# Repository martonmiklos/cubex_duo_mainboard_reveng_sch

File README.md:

# 3D systems CubeX DUO reverse engineered schematic
Reverse engineered schematics for the 3D system's CubeX DUO 3D printer mainboard.

Drawn in Autodesk EAGLE 9.x

Only the stepper drivers for the main axes and the LCD connector have been reverse engineered yet. 

Our goal was to create a simple step-dir driver from the board.

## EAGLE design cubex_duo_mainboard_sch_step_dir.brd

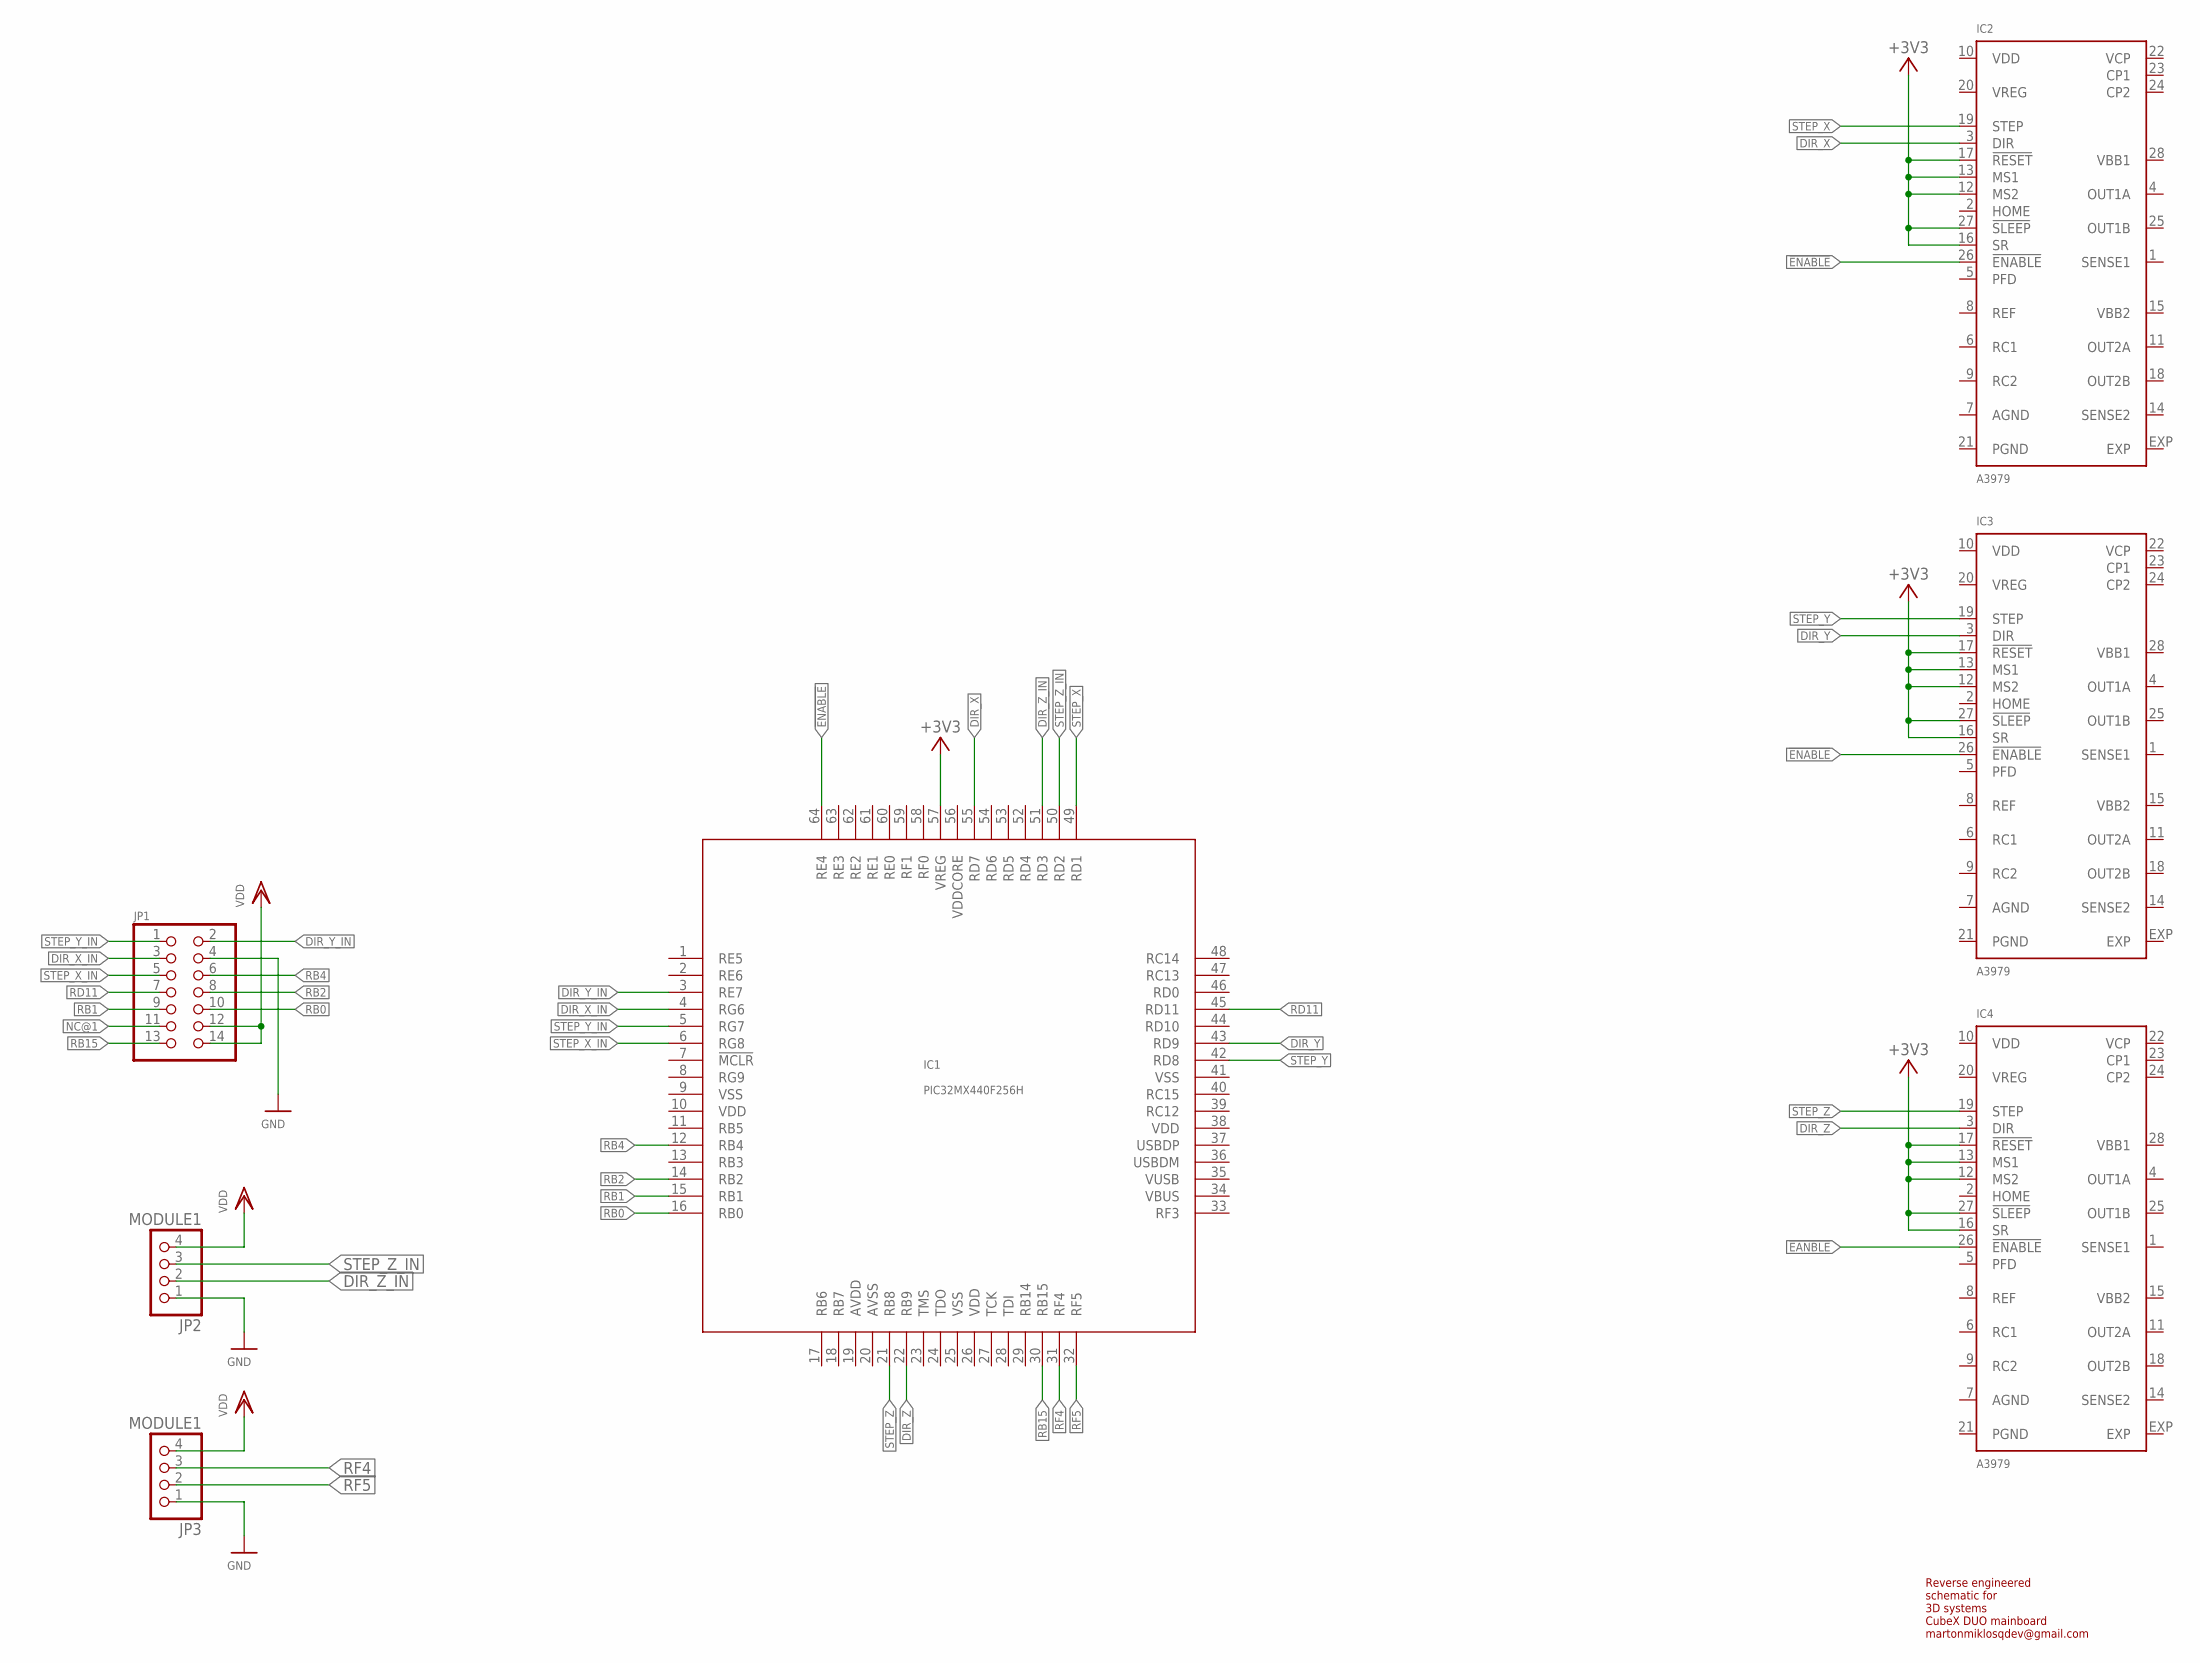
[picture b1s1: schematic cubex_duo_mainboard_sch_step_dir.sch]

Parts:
IC1: PIC32MX440F256H; TQFP64-10X10
IC2, IC3, IC4: A3979; TSSOP28
JP1: PINHD-2X7; 2X07
JP2, JP3: MODULE1; 1X04

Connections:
!EANBLE: IC4.26 (!ENABLE)
!ENABLE: IC1.64 (RE4), IC2.26 (!ENABLE), IC3.26 (!ENABLE)
+3V3: IC1.57 (VREG), IC2.12 (MS2), IC2.13 (MS1), IC2.16 (SR), IC2.17 (!RESET), IC2.27 (!SLEEP), IC3.12 (MS2), IC3.13 (MS1), IC3.16 (SR), IC3.17 (!RESET), IC3.27 (!SLEEP), IC4.12 (MS2), IC4.13 (MS1), IC4.16 (SR), IC4.17 (!RESET), IC4.27 (!SLEEP)
AGND: IC2.7 (AGND), IC3.7 (AGND), IC4.7 (AGND)
AVDD: IC1.19 (AVDD)
AVSS: IC1.20 (AVSS)
DIR_X: IC1.55 (RD7), IC2.3 (DIR)
DIR_X_IN: IC1.4 (RG6), JP1.3
DIR_Y: IC1.43 (RD9), IC3.3 (DIR)
DIR_Y_IN: IC1.3 (RE7), JP1.2
DIR_Z: IC1.22 (RB9), IC4.3 (DIR)
DIR_Z_IN: IC1.51 (RD3), JP2.2
EXP: IC2.EXP, IC3.EXP, IC4.EXP
GND: JP1.4, JP2.1, JP3.1
NC@1: JP1.11
PGND: IC2.21 (PGND), IC3.21 (PGND), IC4.21 (PGND)
RB0: IC1.16 (RB0), JP1.10
RB1: IC1.15 (RB1), JP1.9
RB2: IC1.14 (RB2), JP1.8
RB4: IC1.12 (RB4), JP1.6
RB15: IC1.30 (RB15), JP1.13
RD11: IC1.45 (RD11), JP1.7
RF4: IC1.31 (RF4), JP3.3
RF5: IC1.32 (RF5), JP3.2
STEP_X: IC1.49 (RD1), IC2.19 (STEP)
STEP_X_IN: IC1.6 (RG8), JP1.5
STEP_Y: IC1.42 (RD8), IC3.19 (STEP)
STEP_Y_IN: IC1.5 (RG7), JP1.1
STEP_Z: IC1.21 (RB8), IC4.19 (STEP)
STEP_Z_IN: IC1.50 (RD2), JP2.3
VBB1: IC2.28 (VBB1), IC3.28 (VBB1), IC4.28 (VBB1)
VBB2: IC2.15 (VBB2), IC3.15 (VBB2), IC4.15 (VBB2)
VDD: IC1.10 (VDD), IC1.26 (VDD), IC1.38 (VDD), IC2.10 (VDD), IC3.10 (VDD), IC4.10 (VDD), JP1.12, JP1.14, JP2.4, JP3.4
VDDCORE: IC1.56 (VDDCORE)
VREG: IC2.20 (VREG), IC3.20 (VREG), IC4.20 (VREG)
VSS: IC1.9 (VSS), IC1.25 (VSS), IC1.41 (VSS)

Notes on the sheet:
Reverse engineered schematic for 3D systems CubeX DUO mainboard martonmiklosqdev@gmail.com

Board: 2 copper layers, 7 parts (0 on the bottom side), 31 nets, no tracks yet.

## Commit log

2018-10-26 - Repo init
2018-11-07 Add readout hex
2019-01-25 Added step dir schematics
2019-03-22 Add nENABLE to the step dir sch.
2022-01-17 Added endswitch connection
